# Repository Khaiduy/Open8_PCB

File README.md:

# Open8_PCB

The folder TR4_PGA257 contain:
1. Schematic and layout for PGA257 Socket (PGA257_Socket).
2. Schematic and layout for TEE-PCB version 4.0(TR4).
3. Schematic of the TEE-PGA257_v3.0, used as reference.
4. Pin map and port declaration of chip.
5. Folder ROHM_PCB_thuc is the new PCB that apply Thuc's suggestion.
  - Change SD card and Flash to Pmod module.
    Link: SD card: https://digilent.com/reference/pmod/pmodmicrosd/reference-manual?redirect=1
          Flash: https://digilent.com/reference/pmod/pmodsf3/reference-manual?redirect=
  - Change USB-UART to module: https://www.marutsu.co.jp/GoodsDetail.jsp?q=PL2303SA&salesGoodsCode=137791&shopNo=3
  - Supply clock from SMA only.

Two PCBs for EAGLE is contained:
1. QFP160 socket: the socket and pin connection only.
2. demo_open8: demo board for Open8 in SOTB with pin connection to QFP160 socket.

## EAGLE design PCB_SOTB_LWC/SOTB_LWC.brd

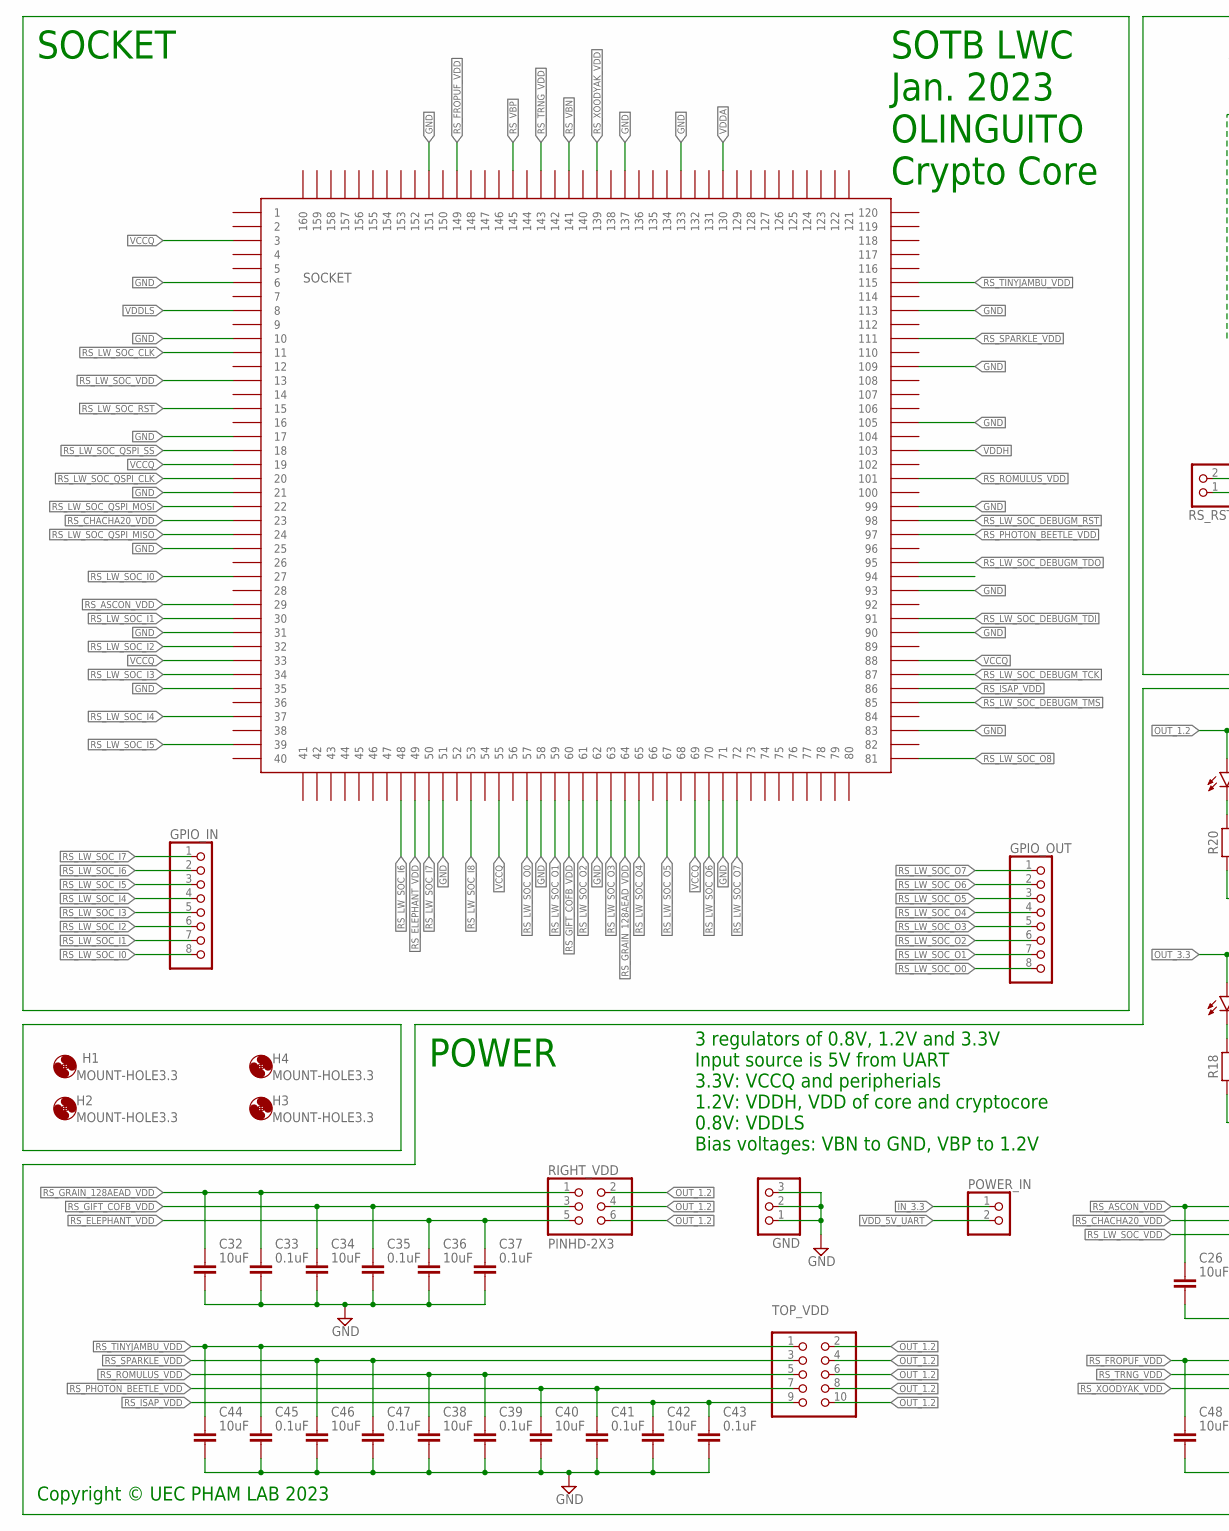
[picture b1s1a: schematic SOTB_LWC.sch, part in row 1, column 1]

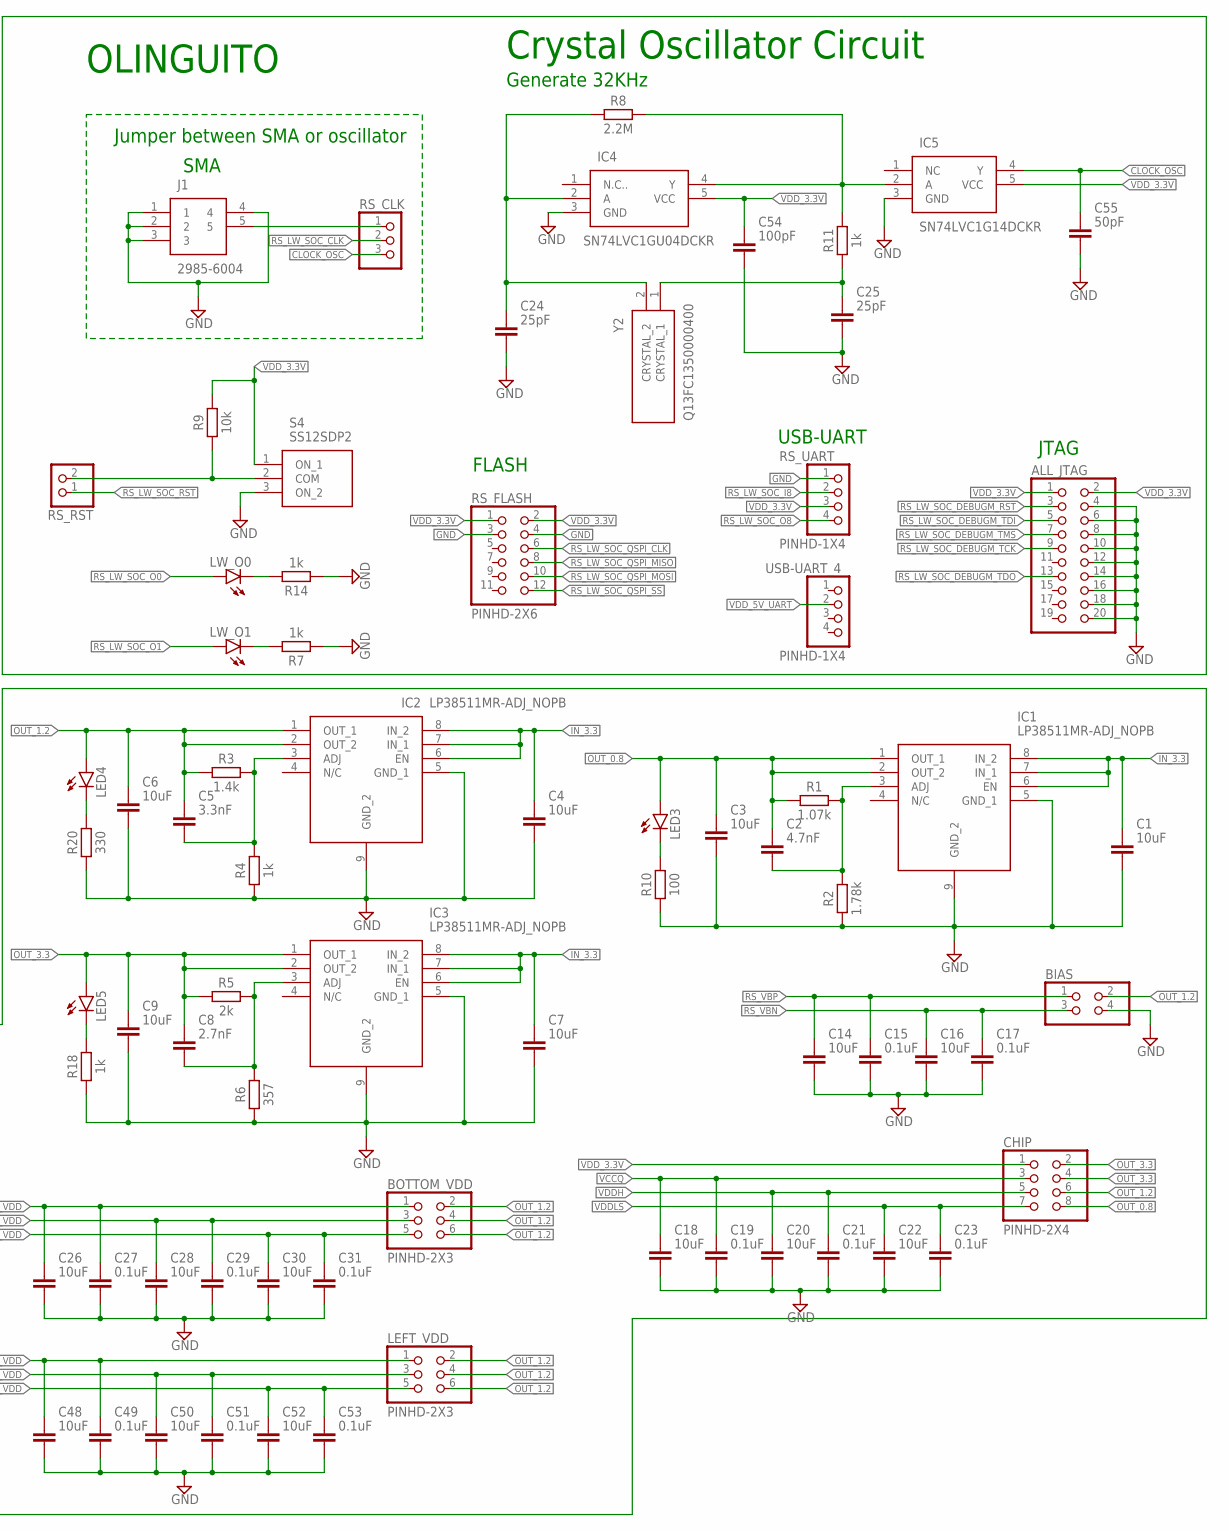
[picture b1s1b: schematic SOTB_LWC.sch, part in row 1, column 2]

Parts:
ALL_JTAG: PINHD-2X10; 2X10
BIAS: PINHD-2X2; 2X02
BOTTOM_VDD: PINHD-2X3; 2X03
C1, C3, C4, C6, C7, C9, C14, C16, C18, C20, C22, C26, C28, C30, C32, C34, C36, C38, C40, C42, C44, C46, C48, C50, C52: 10uF; CAPC3216X135
C2: 4.7nF; CAPC3216X135
C5: 3.3nF; CAPC3216X135
C8: 2.7nF; CAPC3216X135
C15, C17, C19, C21, C23, C27, C29, C31, C33, C35, C37, C39, C41, C43, C45, C47, C49, C51, C53: 0.1uF; CAPC3216X135
C24, C25: 25pF; CAPC2012X110
C54: 100pF; CAPC2012X110
C55: 50pF; CAPC2012X110
CHIP: PINHD-2X4; 2X04
GND: PINHD-1X3; 1X03
GPIO_IN: PINHD-1X8; 1X08
GPIO_OUT: PINHD-1X8; 1X08
H1, H2, H3, H4: MOUNT-HOLE3.3; 3,3
IC1, IC2, IC3: LP38511MR-ADJ_NOPB; SOIC127P600X170-9N
IC4: SN74LVC1GU04DCKR; SOT65P210X110-5N
IC5: SN74LVC1G14DCKR; SOT65P210X110-5N
J1: 2985-6004; 29856004
LED3, LED4, LED5: LEDCHIPLED_0805; CHIPLED_0805
LEFT_VDD: PINHD-2X3; 2X03
LW_O0, LW_O1: LEDCHIPLED_0805; CHIPLED_0805
POWER_IN: PINHD-1X2; 1X02
R1: 1.07k; RESC3216X70
R2: 1.78k; RESC3216X70
R3: 1.4k; RESC3216X70
R4, R7, R11, R14, R18: 1k; RESC3216X70
R5: 2k; RESC3216X70
R6: 357; RESC3216X70
R8: 2.2M; RESC3216X70
R9: 10k; RESC3216X70
R10: 100; RESC3216X70
R20: 330; RESC3216X70
RIGHT_VDD: PINHD-2X3; 2X03
RS_CLK: PINHD-1X3; 1X03
RS_FLASH: PINHD-2X6; 2X06
RS_RST: PINHD-1X2; 1X02
RS_UART: PINHD-1X4; 1X04
S4: SS12SDP2
SOCKET: QFP28-160PIN
TOP_VDD: PINHD-2X5; 2X05
USB-UART_4: PINHD-1X4; 1X04
Y2: Q13FC1350000400

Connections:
CLOCK_OSC: C55.1, IC5.4 (Y), RS_CLK.3
GND: ALL_JTAG.4, ALL_JTAG.6, ALL_JTAG.8, ALL_JTAG.10, ALL_JTAG.12, ALL_JTAG.14, ALL_JTAG.16, ALL_JTAG.18, ALL_JTAG.20, BIAS.4, C1.2, C3.2, C4.2, C6.2, C7.2, C9.2, C14.2, C15.2, C16.2, C17.2, C18.2, C19.2, C20.2, C21.2, C22.2, C23.2, C24.2, C25.2, C26.2, C27.2, C28.2, C29.2, C30.2, C31.2, C32.2, C33.2, C34.2, C35.2, C36.2, C37.2, C38.2, C39.2, C40.2, C41.2, C42.2, C43.2, C44.2, C45.2, C46.2, C47.2, C48.2, C49.2, C50.2, C51.2, C52.2, C53.2, C54.2, C55.2, GND.1, GND.2, GND.3, IC1.5 (GND_1), IC1.9 (GND_2), IC2.5 (GND_1), IC2.9 (GND_2), IC3.5 (GND_1), IC3.9 (GND_2), IC4.3 (GND), IC5.3 (GND), J1.1, J1.2, J1.3, J1.4, R2.1, R4.1, R6.1, R7.1, R10.1, R14.1, R18.1, R20.1, RS_FLASH.3, RS_FLASH.4, RS_UART.1, S4.3 (ON_2), SOCKET.P$6 (6), SOCKET.P$10 (10), SOCKET.P$17 (17), SOCKET.P$21 (21), SOCKET.P$25 (25), SOCKET.P$31 (31), SOCKET.P$35 (35), SOCKET.P$51 (51), SOCKET.P$58 (58), SOCKET.P$62 (62), SOCKET.P$71 (71), SOCKET.P$83 (83), SOCKET.P$90 (90), SOCKET.P$93 (93), SOCKET.P$99 (99), SOCKET.P$105 (105), SOCKET.P$109 (109), SOCKET.P$113 (113), SOCKET.P$133 (133), SOCKET.P$137 (137), SOCKET.P$151 (151)
IN_3.3: C1.1, C4.1, C7.1, IC1.6 (EN), IC1.7 (IN_1), IC1.8 (IN_2), IC2.6 (EN), IC2.7 (IN_1), IC2.8 (IN_2), IC3.6 (EN), IC3.7 (IN_1), IC3.8 (IN_2), POWER_IN.1
unnamed: C2.2, IC1.3 (ADJ), R1.2, R2.2
unnamed: C5.2, IC2.3 (ADJ), R3.2, R4.2
unnamed: C8.2, IC3.3 (ADJ), R5.2, R6.2
unnamed: LW_O1.C, R7.2
unnamed: LW_O0.C, R14.2
unnamed: C24.1, IC4.2 (A), R8.1, Y2.2 (CRYSTAL_2)
unnamed: IC4.4 (Y), IC5.2 (A), R8.2, R11.2
unnamed: LED3.C, R10.2
unnamed: LED4.C, R20.2
unnamed: LED5.C, R18.2
unnamed: C25.1, R11.1, Y2.1 (CRYSTAL_1)
OUT_0.8: C2.1, C3.1, CHIP.8, IC1.1 (OUT_1), IC1.2 (OUT_2), LED3.A, R1.1
OUT_1.2: BIAS.2, BOTTOM_VDD.2, BOTTOM_VDD.4, BOTTOM_VDD.6, C5.1, C6.1, CHIP.6, IC2.1 (OUT_1), IC2.2 (OUT_2), LED4.A, LEFT_VDD.2, LEFT_VDD.4, LEFT_VDD.6, R3.1, RIGHT_VDD.2, RIGHT_VDD.4, RIGHT_VDD.6, TOP_VDD.2, TOP_VDD.4, TOP_VDD.6, TOP_VDD.8, TOP_VDD.10
OUT_3.3: C8.1, C9.1, CHIP.2, CHIP.4, IC3.1 (OUT_1), IC3.2 (OUT_2), LED5.A, R5.1
RST_SW3: R9.1, RS_RST.2, S4.2 (COM)
RS_ASCON_VDD: BOTTOM_VDD.1, C26.1, C27.1, SOCKET.P$29 (29)
RS_CHACHA20_VDD: BOTTOM_VDD.3, C28.1, C29.1, SOCKET.P$23 (23)
RS_ELEPHANT_VDD: C36.1, C37.1, RIGHT_VDD.5, SOCKET.P$49 (49)
RS_FROPUF_VDD: C48.1, C49.1, LEFT_VDD.1, SOCKET.P$149 (149)
RS_GIFT_COFB_VDD: C34.1, C35.1, RIGHT_VDD.3, SOCKET.P$60 (60)
RS_GRAIN_128AEAD_VDD: C32.1, C33.1, RIGHT_VDD.1, SOCKET.P$64 (64)
RS_ISAP_VDD: C42.1, C43.1, SOCKET.P$86 (86), TOP_VDD.9
RS_LW_SOC_CLK: RS_CLK.2, SOCKET.P$11 (11)
RS_LW_SOC_DEBUGM_RST: ALL_JTAG.3, SOCKET.P$98 (98)
RS_LW_SOC_DEBUGM_TCK: ALL_JTAG.9, SOCKET.P$87 (87)
RS_LW_SOC_DEBUGM_TDI: ALL_JTAG.5, SOCKET.P$91 (91)
RS_LW_SOC_DEBUGM_TDO: ALL_JTAG.13, SOCKET.P$95 (95)
RS_LW_SOC_DEBUGM_TMS: ALL_JTAG.7, SOCKET.P$85 (85)
RS_LW_SOC_I0: GPIO_IN.8, SOCKET.P$27 (27)
RS_LW_SOC_I1: GPIO_IN.7, SOCKET.P$30 (30)
RS_LW_SOC_I2: GPIO_IN.6, SOCKET.P$32 (32)
RS_LW_SOC_I3: GPIO_IN.5, SOCKET.P$34 (34)
RS_LW_SOC_I4: GPIO_IN.4, SOCKET.P$37 (37)
RS_LW_SOC_I5: GPIO_IN.3, SOCKET.P$39 (39)
RS_LW_SOC_I6: GPIO_IN.2, SOCKET.P$48 (48)
RS_LW_SOC_I7: GPIO_IN.1, SOCKET.P$50 (50)
RS_LW_SOC_I8: RS_UART.2, SOCKET.P$53 (53)
RS_LW_SOC_O0: GPIO_OUT.8, LW_O0.A, SOCKET.P$57 (57)
RS_LW_SOC_O1: GPIO_OUT.7, LW_O1.A, SOCKET.P$59 (59)
RS_LW_SOC_O2: GPIO_OUT.6, SOCKET.P$61 (61)
RS_LW_SOC_O3: GPIO_OUT.5, SOCKET.P$63 (63)
RS_LW_SOC_O4: GPIO_OUT.4, SOCKET.P$65 (65)
RS_LW_SOC_O5: GPIO_OUT.3, SOCKET.P$67 (67)
RS_LW_SOC_O6: GPIO_OUT.2, SOCKET.P$70 (70)
RS_LW_SOC_O7: GPIO_OUT.1, SOCKET.P$72 (72)
RS_LW_SOC_O8: RS_UART.4, SOCKET.P$81 (81)
RS_LW_SOC_QSPI_CLK: RS_FLASH.6, SOCKET.P$20 (20)
RS_LW_SOC_QSPI_MISO: RS_FLASH.8, SOCKET.P$24 (24)
RS_LW_SOC_QSPI_MOSI: RS_FLASH.10, SOCKET.P$22 (22)
RS_LW_SOC_QSPI_SS: RS_FLASH.12, SOCKET.P$18 (18)
RS_LW_SOC_RST: RS_RST.1, SOCKET.P$15 (15)
RS_LW_SOC_VDD: BOTTOM_VDD.5, C30.1, C31.1, SOCKET.P$13 (13)
RS_PHOTON_BEETLE_VDD: C40.1, C41.1, SOCKET.P$97 (97), TOP_VDD.7
RS_ROMULUS_VDD: C38.1, C39.1, SOCKET.P$101 (101), TOP_VDD.5
RS_SPARKLE_VDD: C46.1, C47.1, SOCKET.P$111 (111), TOP_VDD.3
RS_TINYJAMBU_VDD: C44.1, C45.1, SOCKET.P$115 (115), TOP_VDD.1
RS_TRNG_VDD: C50.1, C51.1, LEFT_VDD.3, SOCKET.P$143 (143)
RS_VBN: BIAS.3, C16.1, C17.1, SOCKET.P$141 (141)
RS_VBP: BIAS.1, C14.1, C15.1, SOCKET.P$145 (145)
RS_XOODYAK_VDD: C52.1, C53.1, LEFT_VDD.5, SOCKET.P$139 (139)
SMA_CLK1: J1.5, RS_CLK.1
VCCQ: C18.1, C19.1, CHIP.3, SOCKET.P$3 (3), SOCKET.P$19 (19), SOCKET.P$33 (33), SOCKET.P$55 (55), SOCKET.P$69 (69), SOCKET.P$88 (88)
VDDA: SOCKET.P$130 (130)
VDDH: C20.1, C21.1, CHIP.5, SOCKET.P$103 (103)
VDDLS: C22.1, C23.1, CHIP.7, SOCKET.P$8 (8)
VDD_3.3V: ALL_JTAG.1, ALL_JTAG.2, C54.1, CHIP.1, IC4.5 (VCC), IC5.5 (VCC), R9.2, RS_FLASH.1, RS_FLASH.2, RS_UART.3, S4.1 (ON_1)
VDD_5V_UART: POWER_IN.2, USB-UART_4.2

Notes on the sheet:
SMA
FLASH
OLINGUITO
Jumper between SMA or oscillator
USB-UART
POWER
3 regulators of 0.8V, 1.2V and 3.3V Input source is 5V from UART 3.3V: VCCQ and peripherials 1.2V: VDDH, VDD of core and cryptocore 0.8V: VDDLS Bias voltages: VBN to GND, VBP to 1.2V
JTAG
Crystal Oscillator Circuit
Generate 32KHz
SOCKET
SOTB LWC Jan. 2023 OLINGUITO Crypto Core
Copyright © UEC PHAM LAB 2023

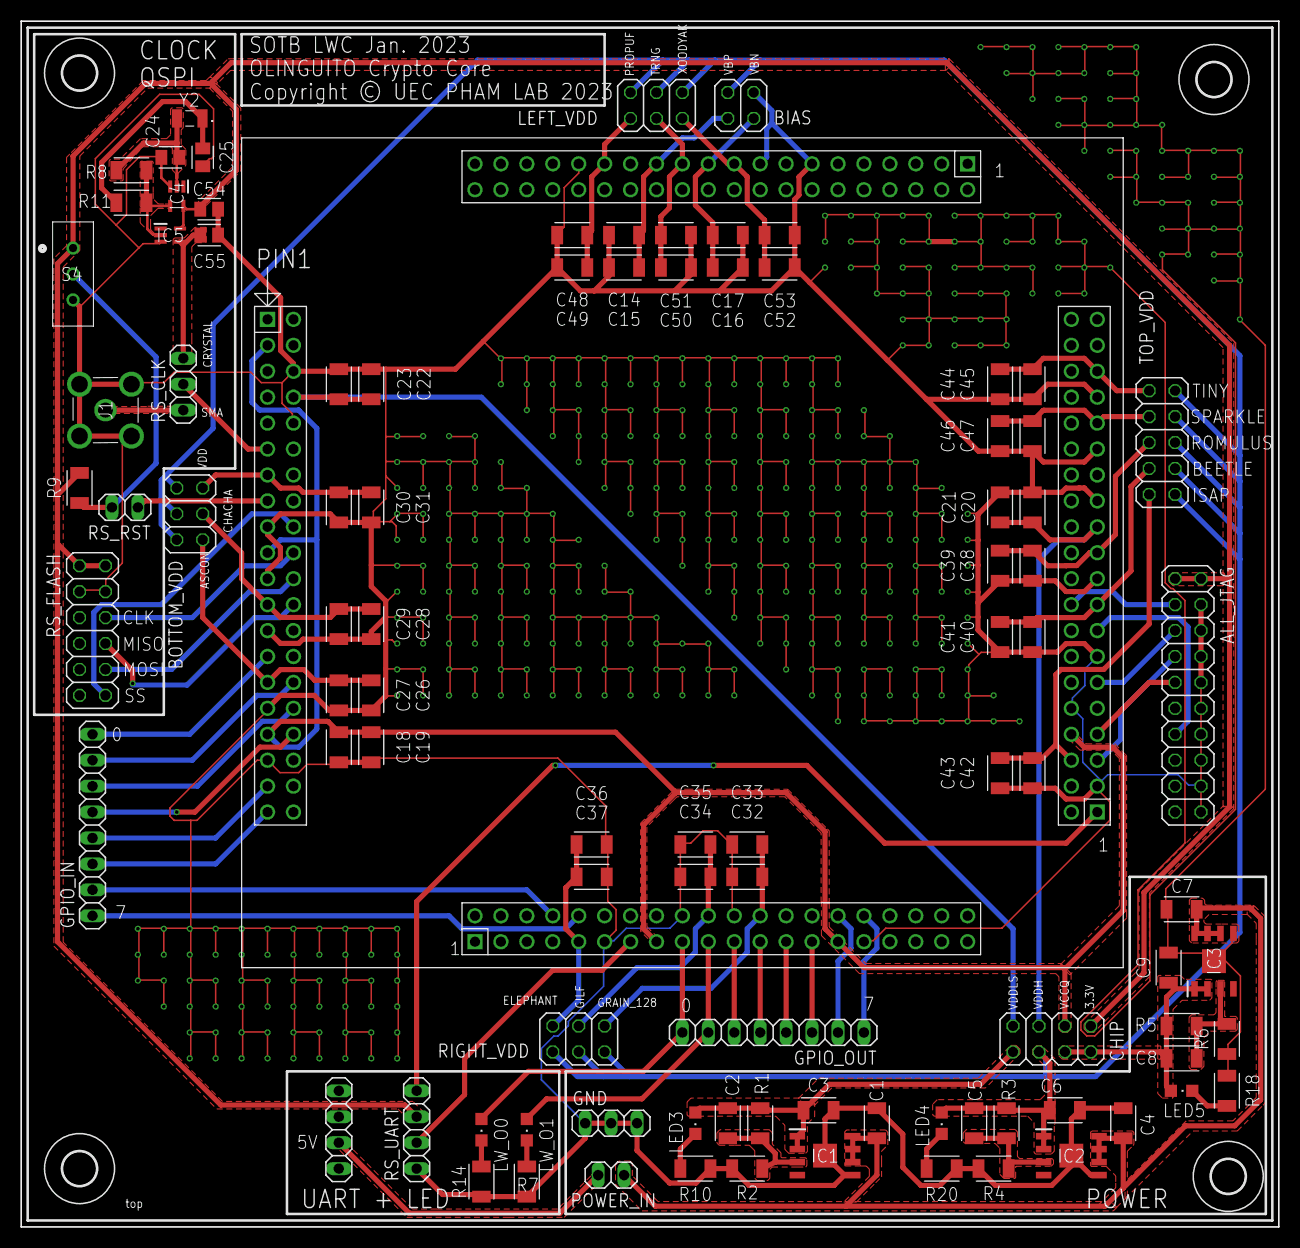
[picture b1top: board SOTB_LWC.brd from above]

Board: 2 copper layers, 123.2 x 118.1 mm, 99 parts (0 on the bottom side), 69 nets.

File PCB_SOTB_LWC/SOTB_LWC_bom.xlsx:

Comment | Designator | Footprint | LCSC Part #（optional）
LEDCHIPLED_0805 | LED3, LED4, LED5, LW_O0, LW_O1 | 805 | C34499
0.1uF | C15, C17, C19, C21, C23, C27, C29, C31, C33, C35, C37, C39, C41, C43, C45, C47,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 | 1206 | C110255
10uF | C1, C3, C4, C6, C7, C9, C14, C16, C18, C20, C22, C26, C28, C30, C32, C34, C36, 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 | 1206 | C13585
100pF | C54 | 805 | C1790
25pF | C24, C25 | 805 | C1807
50pF | C55 | 805 | C1823
2.7nF | C8 | 1206 | C1860
3.3nF | C5 | 1206 | C282859
4.7nF | C2 | 1206 | C9192
1.07k | R1 | 1206 | C290176
1.4k | R3 | 1206 | C102090
1.78k | R2 | 1206 | C706404
100 | R10 | 1206 | C118845
10k | R9 | 1206 | C132649
1k | R4, R7, R11, R14, R18 | 1206 | C1469
2.2M | R8 | 1206 | C111535
2k | R5 | 1206 | C17944
330 | R20 | 1206 | C114944
357 | R6 | 1206 | C205334
LP38511MR-ADJ_NOPB | IC1, IC2, IC3 | SOIC127P600X170 | C113276
Q13FC1350000400 | Y2 | SMD3215-2P | C32346
SN74LVC1G14DCKR | IC5 | SOT65P210X110-5N | C2976657
SN74LVC1GU04DCKR | IC4 | SOT65P210X110-5N | C485082

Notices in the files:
parts and their libraries:
SparkFun-Resistors: Licensing: Creative Commons ShareAlike 4.0 International - https://creativecommons.org/licenses/by-sa/4.0
